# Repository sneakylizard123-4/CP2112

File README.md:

# CP2112 USB-to-SMBus Bridge Board

A small board based on the CP2112
USB to SMBus/I2C

## Custom Features

- CP2112 HID USB-to-SMBus/I2C - no driver install necessary
- USB-C with ESD protection
- On-board 1.8V LDO
- 8x status LEDs
- Breakout headers for I2C/SMBus and GPIO
- Slide switch for VIO selection (3.3v/1.8v)
- 4-layer PCB, 50 x 37.5 mm, 4x M3 mounting holes

## How It Works

USB -> CP2112 -> I2C

| Block | Part | Role |
|-------|------|------|
| Bridge | CP2112 | HID USB-to-UART/I2C bridge, crystal-less |
| USB | USB_C_Receptacle_USB2.0_16P (HRO TYPE-C-31-M-12) | Host connection |
| Protection | USBLC6-2SC6 | ESD clamp on D+/D- |
| Power | TLV75718PDBV | 1.8V LDO, powers VIO rail |
| I/O | 2x5 + 1x4 pin headers | UART / SMBus / GPIO access |

### Power Tree

```mermaid
flowchart LR
    VBUS["USB-C VBUS +5V"] --> P5["+5V"]
    P5 --> U2["CP2112 VDD"]
    U2 --> R33["+3.3V internal reg"]
    P5 --> U3["TLV75718PDBV LDO"]
    U3 --> R18["+1.8V"]
    R33 --> SW["SW1 VIO select"]
    R18 --> SW
    SW --> VIO["VIO rail: CP2112, LEDs, pull-ups, headers"]
```

## PCB Design

- 4-layer, 50.00 x 37.50 mm, 1.6 mm, 6 copper zones
- USB kept close to the CP2112, D+/D- routed short on the top layer
- Decoupling caps placed at the CP2112 and LDO pins
- All passives 0805 for easy hand assembly

## Firmware

No firmware needed!!

## Usage

- Connect USB
- Connect I2C/SMBus device

Power comes from the USB-C port

## BOM (Bill of Materials)

| Qty | Designator | Value | Package | Part / Link |
|-----|------------|-------|---------|-------------|
| 1 | C1 | 4.7 uF | 0805 | [C1779](https://www.lcsc.com/product-detail/C1779.html) |
| 4 | C10, C4, C6, C8 | 10 uF | 0805 | [C15850](https://www.lcsc.com/product-detail/C15850.html) |
| 1 | C2 | 1 uF | 0805 | [C28323](https://www.lcsc.com/product-detail/C28323.html) |
| 4 | C3, C5, C7, C9 | 100 nF | 0805 | [C49678](https://www.lcsc.com/product-detail/C49678.html) |
| 8 | D1-D8 | LED | 0805 | [C84256](https://www.lcsc.com/product-detail/C84256.html) |
| 1 | J1 | USB-C receptacle USB 2.0 | HRO TYPE-C-31-M-12 | [C165948](https://www.lcsc.com/product-detail/C165948.html) |
| 2 | J2, J4 | Pin socket 1x04 | 2.54 mm | [C2718488](https://www.lcsc.com/product-detail/C2718488.html) |
| 1 | J3 | Pin socket 2x05 | 2.54 mm | [C30419](https://jlcpcb.com/partdetail/31176-2_54mm25p/C30419) |
| 2 | R1, R2 | 5.1k | 0805 | [C27834](https://www.lcsc.com/product-detail/C27834.html) |
| 8 | R6-R13 | 1k | 0805 | [C17513](https://www.lcsc.com/product-detail/C17513.html) |
| 1 | R3 | 10k | 0805 | [C17414](https://www.lcsc.com/product-detail/C17414.html) |
| 2 | R4, R5 | 4.7k | 0805 | [C17673](https://www.lcsc.com/product-detail/C17673.html) |
| 1 | SW1 | Slide switch SPDT | CK OS102011MS2Q | [C221829](https://www.lcsc.com/product-detail/C221829.html) |
| 1 | U1 | USBLC6-2SC6 | SOT-23-6 | [C7519](https://www.lcsc.com/product-detail/C7519.html) |
| 1 | U2 | CP2112 | QFN-24 4x4 mm | [C2678020](https://www.lcsc.com/product-detail/C2678020.html) |
| 1 | U3 | TLV75718PDBV | SOT-23-5 | [C507270](https://www.lcsc.com/product-detail/C507270.html) |

Full BOM with prices and MOQ at [BOM.csv](BOM.csv)

## Production

standard JLCPCB 4-layer PCB

## Repository Structure

```
├── kicad/            # PCB source files
│   └── production/   # Gerbers, BOM + positions csv
├── cad/              # .step export + native CAD source
├── firmware/         # Firmware source code (if any)
├── images/           # renders/ + schematic/ screenshots
└── JOURNAL.md        # Work journal
```

## Known Issues

- Hasn't been built yet

## Credits & Inspiration

- CP2112 Datasheet for reference design

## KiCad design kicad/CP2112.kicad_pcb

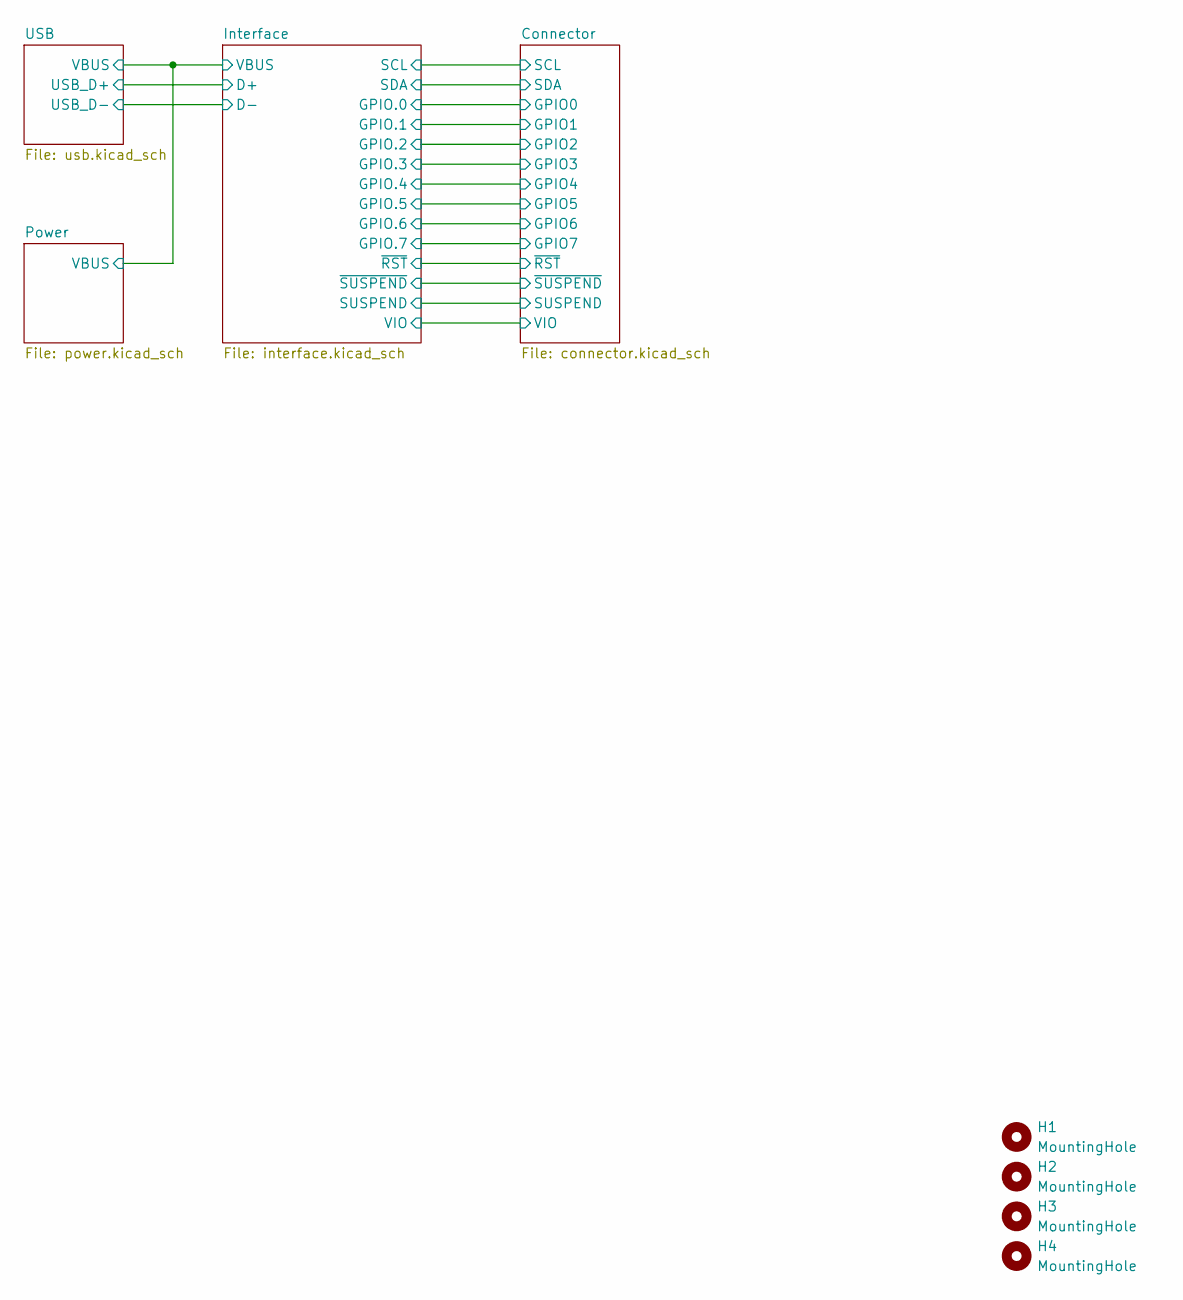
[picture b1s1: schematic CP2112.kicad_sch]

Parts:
H1, H2, H3, H4: MountingHole; MountingHole_3.2mm_M3

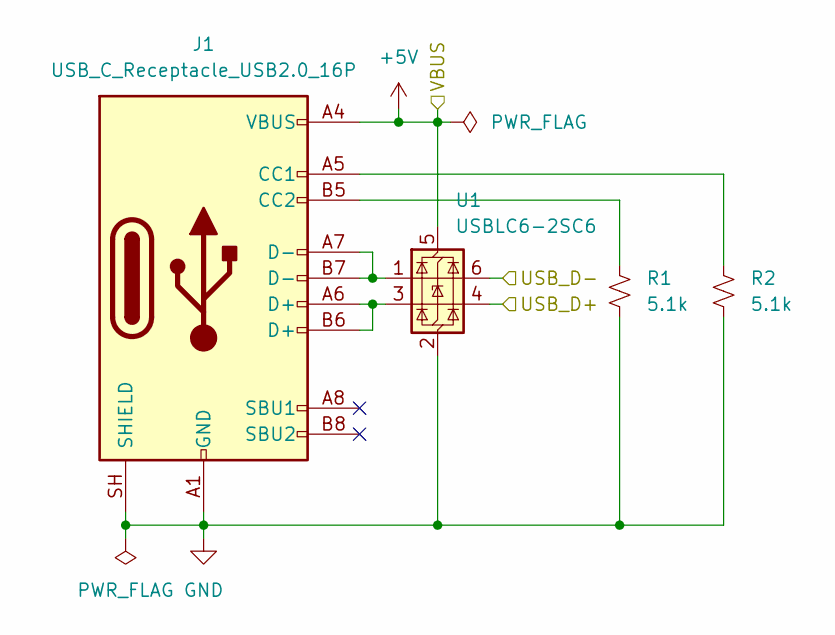
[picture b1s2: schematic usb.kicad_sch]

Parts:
J1: USB_C_Receptacle_USB2.0_16P; USB_C_Receptacle_HRO_TYPE-C-31-M-12
R1, R2: 5.1k; R_0805_2012Metric
U1: USBLC6-2SC6; SOT-23-6

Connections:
+5V: J1.A4 (VBUS), J1.A9 (VBUS), J1.B4 (VBUS), J1.B9 (VBUS), U1.5 (VBUS); also elsewhere on the board
/Interface/D+: U1.4 (I/O2); also elsewhere on the board
/Interface/D-: U1.6 (I/O1); also elsewhere on the board
GND: J1.A1 (GND), J1.A12 (GND), J1.B1 (GND), J1.B12 (GND), J1.SH (SHIELD), R1.2, R2.2, U1.2 (GND); also elsewhere on the board
unnamed: J1.A5 (CC1), R2.1
unnamed: J1.B5 (CC2), R1.1
unnamed: J1.A6 (D+), J1.B6 (D+), U1.3 (I/O2)
unnamed: J1.A7 (D-), J1.B7 (D-), U1.1 (I/O1)

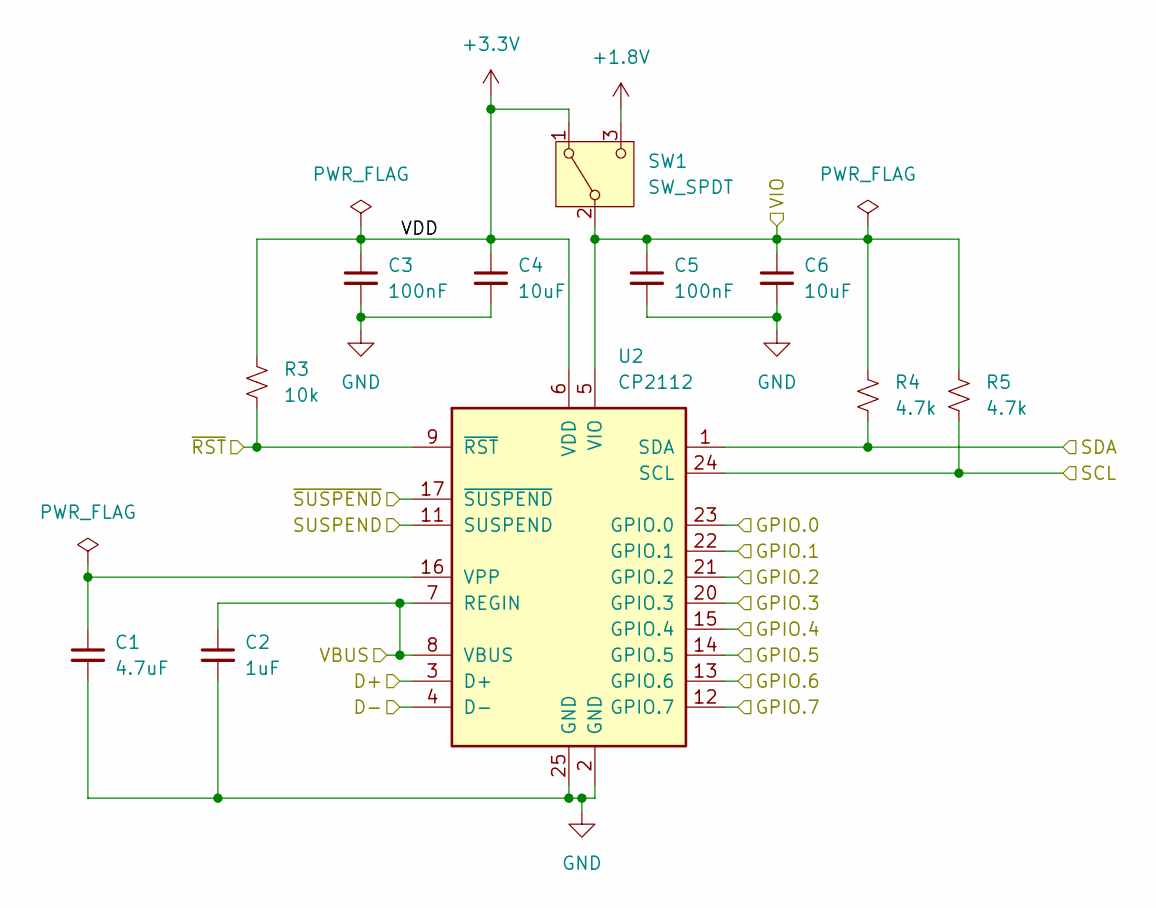
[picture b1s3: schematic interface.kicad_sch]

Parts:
C1: 4.7uF; C_0805_2012Metric
C2: 1uF; C_0805_2012Metric
C3, C5: 100nF; C_0805_2012Metric
C4, C6: 10uF; C_0805_2012Metric
R3: 10k; R_0805_2012Metric
R4, R5: 4.7k; R_0805_2012Metric
SW1: SW_SPDT; SW_Slide_SPDT_Straight_CK_OS102011MS2Q
U2: CP2112; QFN-24-1EP_4x4mm_P0.5mm_EP2.6x2.6mm

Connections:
+1.8V: SW1.3 (C); also elsewhere on the board
+3.3V: C3.1, C4.1, R3.1, SW1.1 (A), U2.6 (VDD); also elsewhere on the board
+5V: C2.1, U2.7 (REGIN), U2.8 (VBUS); also elsewhere on the board
/Connector/GPIO0: U2.23 (GPIO.0); also elsewhere on the board
/Connector/GPIO1: U2.22 (GPIO.1); also elsewhere on the board
/Connector/GPIO2: U2.21 (GPIO.2); also elsewhere on the board
/Connector/GPIO3: U2.20 (GPIO.3); also elsewhere on the board
/Connector/GPIO4: U2.15 (GPIO.4); also elsewhere on the board
/Connector/GPIO5: U2.14 (GPIO.5); also elsewhere on the board
/Connector/GPIO6: U2.13 (GPIO.6); also elsewhere on the board
/Connector/GPIO7: U2.12 (GPIO.7); also elsewhere on the board
/Connector/SCL: R5.2, U2.24 (SCL); also elsewhere on the board
/Connector/SDA: R4.2, U2.1 (SDA); also elsewhere on the board
/Connector/SUSPEND: U2.11 (SUSPEND); also elsewhere on the board
/Connector/VIO: C5.1, C6.1, R4.1, R5.1, SW1.2 (B), U2.5 (VIO); also elsewhere on the board
/Connector/~RST: R3.2, U2.9 (~RST); also elsewhere on the board
/Connector/~SUSPEND: U2.17 (~SUSPEND); also elsewhere on the board
/Interface/D+: U2.3 (D+); also elsewhere on the board
/Interface/D-: U2.4 (D-); also elsewhere on the board
GND: C1.2, C2.2, C3.2, C4.2, C5.2, C6.2, U2.2 (GND), U2.25 (GND); also elsewhere on the board
unnamed: C1.1, U2.16 (VPP)

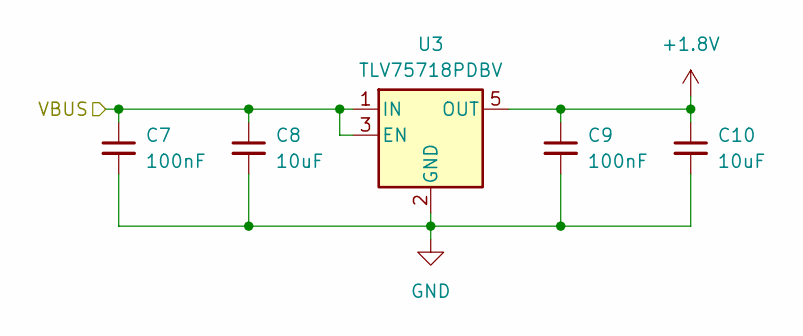
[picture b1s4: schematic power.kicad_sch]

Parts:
C7, C9: 100nF; C_0805_2012Metric
C8, C10: 10uF; C_0805_2012Metric
U3: TLV75718PDBV; SOT-23-5

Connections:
+1.8V: C9.1, C10.1, U3.5 (OUT); also elsewhere on the board
+5V: C7.1, C8.1, U3.1 (IN), U3.3 (EN); also elsewhere on the board
GND: C7.2, C8.2, C9.2, C10.2, U3.2 (GND); also elsewhere on the board

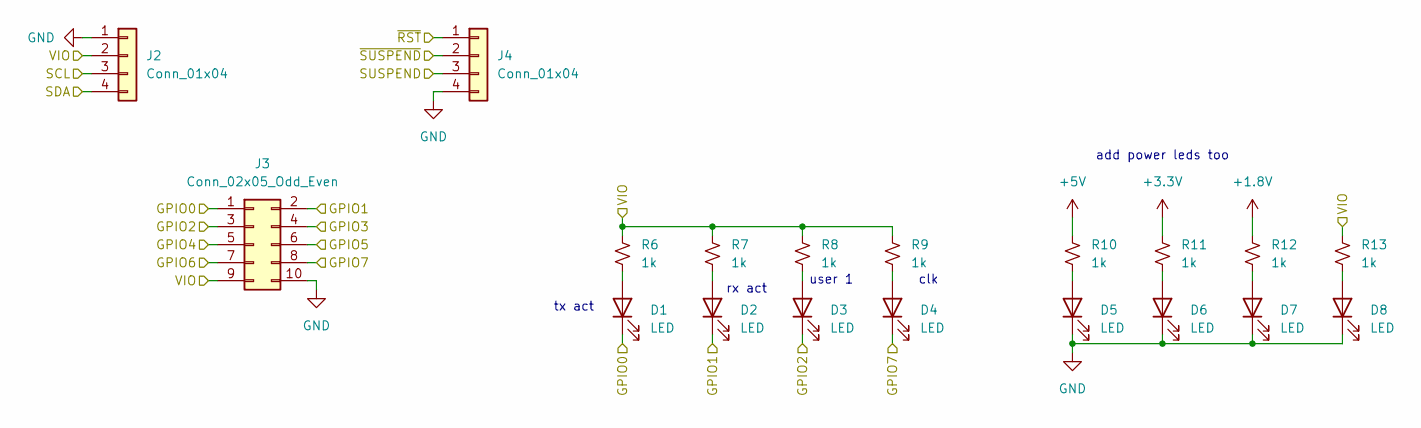
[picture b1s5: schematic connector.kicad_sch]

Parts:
D1, D2, D3, D4, D5, D6, D7, D8: LED; LED_0805_2012Metric
J2, J4: Conn_01x04; PinSocket_1x04_P2.54mm_Vertical
J3: Conn_02x05_Odd_Even; PinSocket_2x05_P2.54mm_Vertical
R6, R7, R8, R9, R10, R11, R12, R13: 1k; R_0805_2012Metric

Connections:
+1.8V: R12.1; also elsewhere on the board
+3.3V: R11.1; also elsewhere on the board
+5V: R10.1; also elsewhere on the board
/Connector/GPIO0: D1.1 (K), J3.1; also elsewhere on the board
/Connector/GPIO1: D2.1 (K), J3.2; also elsewhere on the board
/Connector/GPIO2: D3.1 (K), J3.3; also elsewhere on the board
/Connector/GPIO3: J3.4; also elsewhere on the board
/Connector/GPIO4: J3.5; also elsewhere on the board
/Connector/GPIO5: J3.6; also elsewhere on the board
/Connector/GPIO6: J3.7; also elsewhere on the board
/Connector/GPIO7: D4.1 (K), J3.8; also elsewhere on the board
/Connector/SCL: J2.3; also elsewhere on the board
/Connector/SDA: J2.4; also elsewhere on the board
/Connector/SUSPEND: J4.3; also elsewhere on the board
/Connector/VIO: J2.2, J3.9, R6.1, R7.1, R8.1, R9.1, R13.1; also elsewhere on the board
/Connector/~RST: J4.1; also elsewhere on the board
/Connector/~SUSPEND: J4.2; also elsewhere on the board
GND: D5.1 (K), D6.1 (K), D7.1 (K), D8.1 (K), J2.1, J3.10, J4.4; also elsewhere on the board
unnamed: D1.2 (A), R6.2
unnamed: D2.2 (A), R7.2
unnamed: D3.2 (A), R8.2
unnamed: D4.2 (A), R9.2
unnamed: D5.2 (A), R10.2
unnamed: D6.2 (A), R11.2
unnamed: D7.2 (A), R12.2
unnamed: D8.2 (A), R13.2

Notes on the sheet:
clk
add power leds too
tx act
rx act
user 1

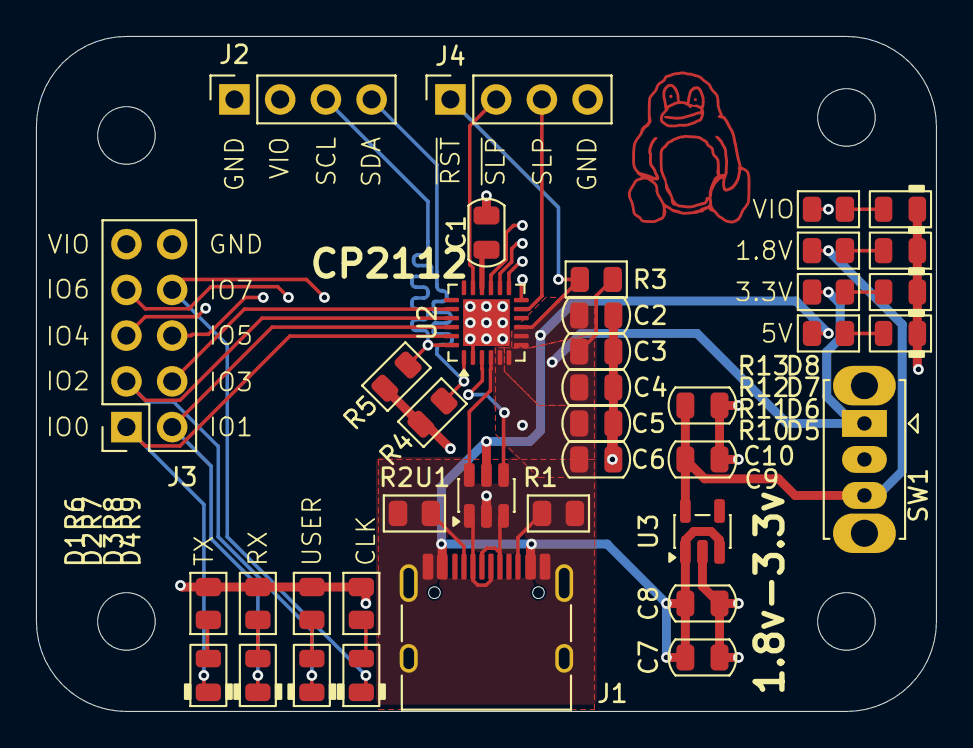
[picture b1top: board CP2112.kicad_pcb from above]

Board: 4 copper layers, 50.0 x 37.5 mm, 43 parts (0 on the bottom side), 33 nets.

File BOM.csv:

Designator,Value,Footprint,Qty Needed,MOQ,Qty Ordered,LCSC Part #,Supplier Link,Unit Price @ MOQ (USD),Line Total (USD)
R1 R2,5.1k,0805,2,100,100,C27834,https://www.lcsc.com/product-detail/C27834.html,0.006,0.60
R3,10k,0805,1,100,100,C17414,https://www.lcsc.com/product-detail/C17414.html,0.0039,0.39
R4 R5,4.7k,0805,2,100,100,C17673,https://www.lcsc.com/product-detail/C17673.html,0.0051,0.51
R6-R13,1k,0805,8,100,100,C17513,https://www.lcsc.com/product-detail/C17513.html,0.0041,0.41
C1,4.7uF,0805,1,20,20,C1779,https://www.lcsc.com/product-detail/C1779.html,0.0348,0.70
C2,1uF,0805,1,10,10,C28323,https://www.lcsc.com/product-detail/C28323.html,0.0403,0.40
C3 C5 C7 C9,100nF,0805,4,20,20,C49678,https://www.lcsc.com/product-detail/C49678.html,0.0195,0.39
C4 C6 C8 C10,10uF,0805,4,20,20,C15850,https://www.lcsc.com/product-detail/C15850.html,0.0852,1.70
D1-D8,LED red,0805,8,50,50,C84256,https://www.lcsc.com/product-detail/C84256.html,0.0135,0.68
J1,USB Type-C,16P USB2.0,1,5,5,C165948,https://www.lcsc.com/product-detail/C165948.html,0.1879,0.94
J2 J4,Pin socket 1x4,THT 2.54mm,2,10,10,C2718488,https://www.lcsc.com/product-detail/C2718488.html,0.0793,0.79
J3,Pin socket 2x5,THT 2.54mm,1,5,5,C30419,https://jlcpcb.com/partdetail/31176-2_54mm25p/C30419,0.1182,0.59
SW1,Slide switch SPDT,THT C&K OS102011,1,1,1,C221829,https://www.lcsc.com/product-detail/C221829.html,0.662,0.66
U1,USBLC6-2SC6,SOT-23-6,1,5,5,C7519,https://www.lcsc.com/product-detail/C7519.html,0.1782,0.89
U2,CP2112-F03-GMR,QFN-24 4x4,1,1,1,C2678020,https://www.lcsc.com/product-detail/C2678020.html,6.2024,6.20
U3,TLV75718PDBVR,SOT-23-5,1,5,5,C507270,https://www.lcsc.com/product-detail/C507270.html,0.3151,1.58
TOTAL,,,,,,,,17.43
